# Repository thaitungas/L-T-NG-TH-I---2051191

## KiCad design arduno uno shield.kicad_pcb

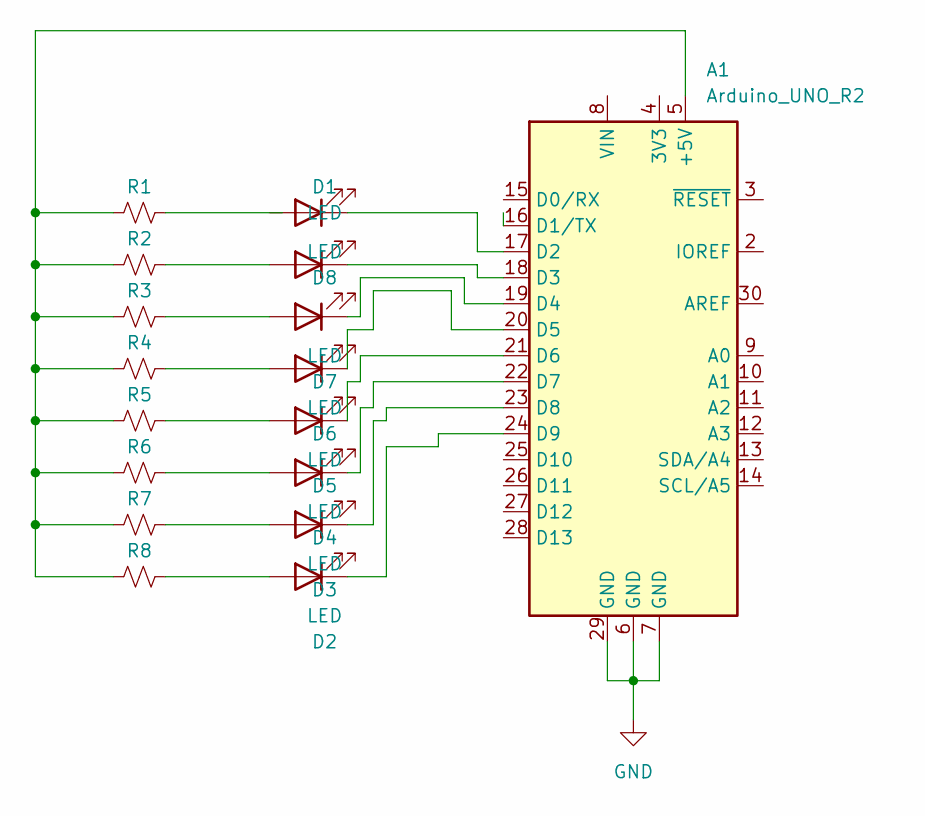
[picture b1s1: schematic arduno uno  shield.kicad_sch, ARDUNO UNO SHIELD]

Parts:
A1: Arduino_UNO_R2
D1, D2, D3, D4, D5, D6: LED; LED_0603_1608Metric
D7, D8: LED; LED_0201_0603Metric
R1: R1; R_0201_0603Metric
R2: R2; R_0201_0603Metric
R3: R3; R_0201_0603Metric
R4: R4; R_0201_0603Metric
R5: R5; R_0201_0603Metric
R6: R6; R_0201_0603Metric
R7: R7; R_0201_0603Metric
R8: R8; R_0201_0603Metric

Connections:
GND: A1.6 (GND), A1.7 (GND), A1.29 (GND)
unnamed: A1.5 (+5V), R1.2, R2.2, R3.2, R4.2, R5.2, R6.2, R7.2, R8.2
unnamed: A1.17 (D2), D8.1 (K)
unnamed: A1.18 (D3), D1.1 (K)
unnamed: A1.19 (D4), D7.1 (K)
unnamed: A1.20 (D5), D6.1 (K)
unnamed: A1.21 (D6), D5.1 (K)
unnamed: A1.22 (D7), D4.1 (K)
unnamed: A1.23 (D8), D3.1 (K)
unnamed: A1.24 (D9), D2.1 (K)
unnamed: D1.2 (A), R2.1
unnamed: D2.2 (A), R8.1
unnamed: D3.2 (A), R7.1
unnamed: D4.2 (A), R6.1
unnamed: D5.2 (A), R5.1
unnamed: D6.2 (A), R4.1
unnamed: D7.2 (A), R3.1

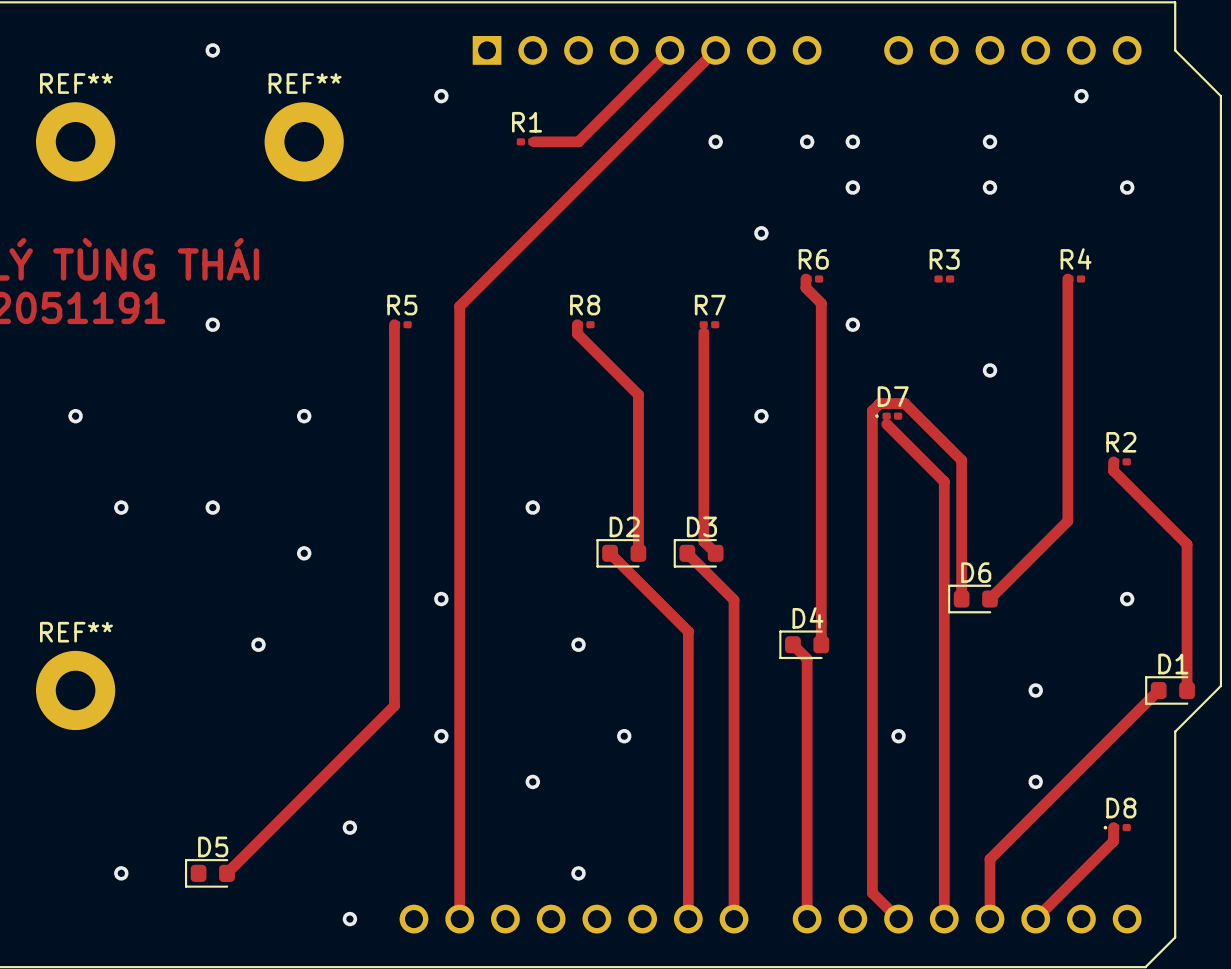
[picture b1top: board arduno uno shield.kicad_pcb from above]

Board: 2 copper layers, 17 parts (0 on the bottom side), 17 nets.
